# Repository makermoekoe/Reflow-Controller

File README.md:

# Reflow-Controller

</a>

The Reflow-Controller was built to control different kinds of reflow ovens, hotplates and whatever is coming to my mind in the future. It is based on the ESP32-S2 ([datasheet](https://www.espressif.com/sites/default/files/documentation/esp32-s2_datasheet_en.pdf)) and thus can be programmed to be used with a WiFi App or whatever. Nevertheless, it has an onboard OLED display and three buttons included to be used as a standalone solution either.

The [Youtube video](https://youtu.be/nffLDqJwJ3Q) shows the assembly of a complete reflow oven system and the first tests.

## Build & flash :
Using Visual Studio : Import "code" folder as project folder. Connect the pcb via usb, put the S1 switch to the lower position, hold and press GPIO0-button while resetting with the reset-button. ESP32 should come up as a serial port device. Select that corresponding port for flashing. Edit platformio.ini file and set the upload_port setting corresponding to your serial port device (COMxx on Windows, /dev/ttyUSBx on linux or /dev/cu.usbmodem01 as stated by makermoekoe (original projects author).
Press compile & upload button.

Using Arduino IDE :
Import main.cpp file contents as a new sketch.
Add "https://raw.githubusercontent.com/espressif/arduino-esp32/gh-pages/package_esp32_dev_index.json" as additional board manager URL in Arduino IDE preferences.
Connect the pcb via usb, put the S1 switch to the lower position, hold and press GPIO0-button while resetting with the reset-button. ESP32 should come up as a serial port device. Select that corresponding port for flashing in Arduino (Port setting where the board selection is also located, in "Tools" - Menu)
Then select ESP32S2-Dev Module as board in Arduino. You can make all ESP32-related flash & chip configs there too. The settings I use are :
-"Use CDC on boot" - Enabled
-"CPU Frequency" - 240MHz
-"Core Debug Level" - Warn

All others left by default / select the ones you think fits best.

Libraries required as dependency for the project in Arduino (as for 2.0.3 version I currently use, install them via Arduino Library Manager) :
- PID by Brett Beauregard - v 1.2.1
- FastLED by Daniel Garcia - v 3.5.0
- U8G2 by Oliver Kraus - v 2.33.15
- MAX6675 Library by Adafruit - v 1.1.0
- Smoothed by Matthew Fryer - v 1.2
- ESPAsync-WifiManager and all it`s dependencies (install via IDE library manager) - https://github.com/khoih-prog/ESPAsync_WiFiManager

Lib-versions are the latest ones when writing this.

## Wifi - Setup :
Wifi will (currently!?) NOT work correctly when the board is powered by USB.
This means, you can flash via USB without external power to the board, but, as the initial wifi-setup is blocking the normal program, you will need to power via external power, to get wifi set up correctly. Once wifi is set up, "normal" program will run as soon as wifi connected.
Make sure to select the default 4MB flash partitioning scheme with SPIFFS when flashing.
Process should be done as follows :
Compile & flash => switch to external power => configure wifi by connecting to the esp32-provided AP => restart board on external. You can and should monitor the serial output via USB for the first startup via serial console anyhow, as it will show you debug info and the default wifi-password for the config ap. The caption page of the AP to do the wifi settings is listening on 192.168.4.1:80 once the AP is up.

## OTA-Flash :
Once the board is connected to wifi, you can flash it over the air from then on. Simply select the network-connection port in Arduino, that should come up a few seconds after the board is powered and connected to wifi. Only downside/bug I found so far, is that often the flashing process in Arduino doesnt get the successful flash response and therefore keeps hanging in flash mechanism - making a restart of the IDE necessary. Apart from that, OTA works fine.

(Note from p1ngb4ck, adding this section : ) At the time of writing this, I did not yet find out, how to make the esptool.py settings in Visual Studio Code to be able to make the ESP32 chip settings (USB-CDC, SPIFFS etc etc). Therefore I currently use Arduino 2.0.3 IDE myself. Visual Studio Code has the advantage though, not to have to download&install dependencies (libraries) manually though. If anybody share some light into how to make these settings correctly in Visual Studio Code - you are mostly welcome to add this info by posting to issues section. TY.

Lots of thanks for this great project to makermoekoe. Please watch his video !!!

## Features of the PCB:

- ESP32-S2 MCU
- 2x MAX6675 thermocouple sensor input
- 2x Fan output (inductive loads/flyback diodes included)
- 2x Solid state relay output
- 3x User button
- 1x APA102 user LED
- 1x Buzzer
- 1x Servo motor output
- 0,96" OLED display
- Optional ACDC converter (HLK-PM05, HLK-PM12) which can be separated if not used
- Optional I2C (QWIIC) connector

## GPIOs

The ESP32-S2 is connected like this:

Function | GPIO | Mode
-------- | -------- | --------
SSR1 | GPIO1 | Output
SSR2 | GPIO2 | Output
Servo | GPIO3 | Output
Fan1 | GPIO5 | Output
Fan2 | GPIO6 | Output
CLK | GPIO7 | SPI
MISO | GPIO9 | SPI
MOSI | GPIO11 | SPI
CS1 | GPIO12 | SPI
CS2 | GPIO13 | SPI
Buzzer | GPIO15 | Output
USB D- | GPIO19 | CDC
USB D+ | GPIO20 | CDC
SDA | GPIO33 | I2C
SCL | GPIO35 | I2C
Button1 | GPIO36 | Input
Button2 | GPIO39 | Input
Button3 | GPIO40 | Input
LED CLK | GPIO37 | LED
LED DATA | GPIO38 | LED
OLED RST | GPIO45 | Output

## ACDC power supply

The upper part of the PCB can be used as a power supply for the whole board as well as the higher voltage outputs (SSRs, Fans). If not used, it can be separated from the main board and may be used in another project where an ACDC adapter is needed.

The main board is equipped with an LM1117 3.3v voltage regulator which can be feed with 15v max. The output voltage of the ACDC power supply is the voltage for the SSR and the fan output channels. If you wanna use a servo motor in your project, make sure that the power supply has the correct voltage for the motor (probably 5v).

The HLK-PMXX module for the upper part of the PCB can be placed in two ways - on the bottom or on the top side. This gives the possibility to mount the whole PCB behind an acrylic glass (or whatever) so that the buttons as well as the OLED display are accessible. The two jumpers can then be used to select which signal is VCC and which one is GND. **Keep in mind that there are high voltage pins on the top side of the PCB when mounting the power supply on the bottom side! I've designed a 3D-printable cover, so that these pins cannot be touched accidentally. (Should be mounted in both cases)**

The board can also be powered via USB-C, but keep in mind that the output channels and the servo motor are not powered in this case (initially it is just available for flashing the board).

## Case & Spacer

As I wanna hide the whole PCB behind an acrylic glass (transparent) I've designed a simple case for the high voltage pins at the top and a spacer at the bottom of the PCB. In the end, the acrylic glass will be laser-cutted with some bridges for the buttons. Distance between PCB and acrylic glass is 5mm.

</a>

## Assembled reflow oven

</a>

</a>

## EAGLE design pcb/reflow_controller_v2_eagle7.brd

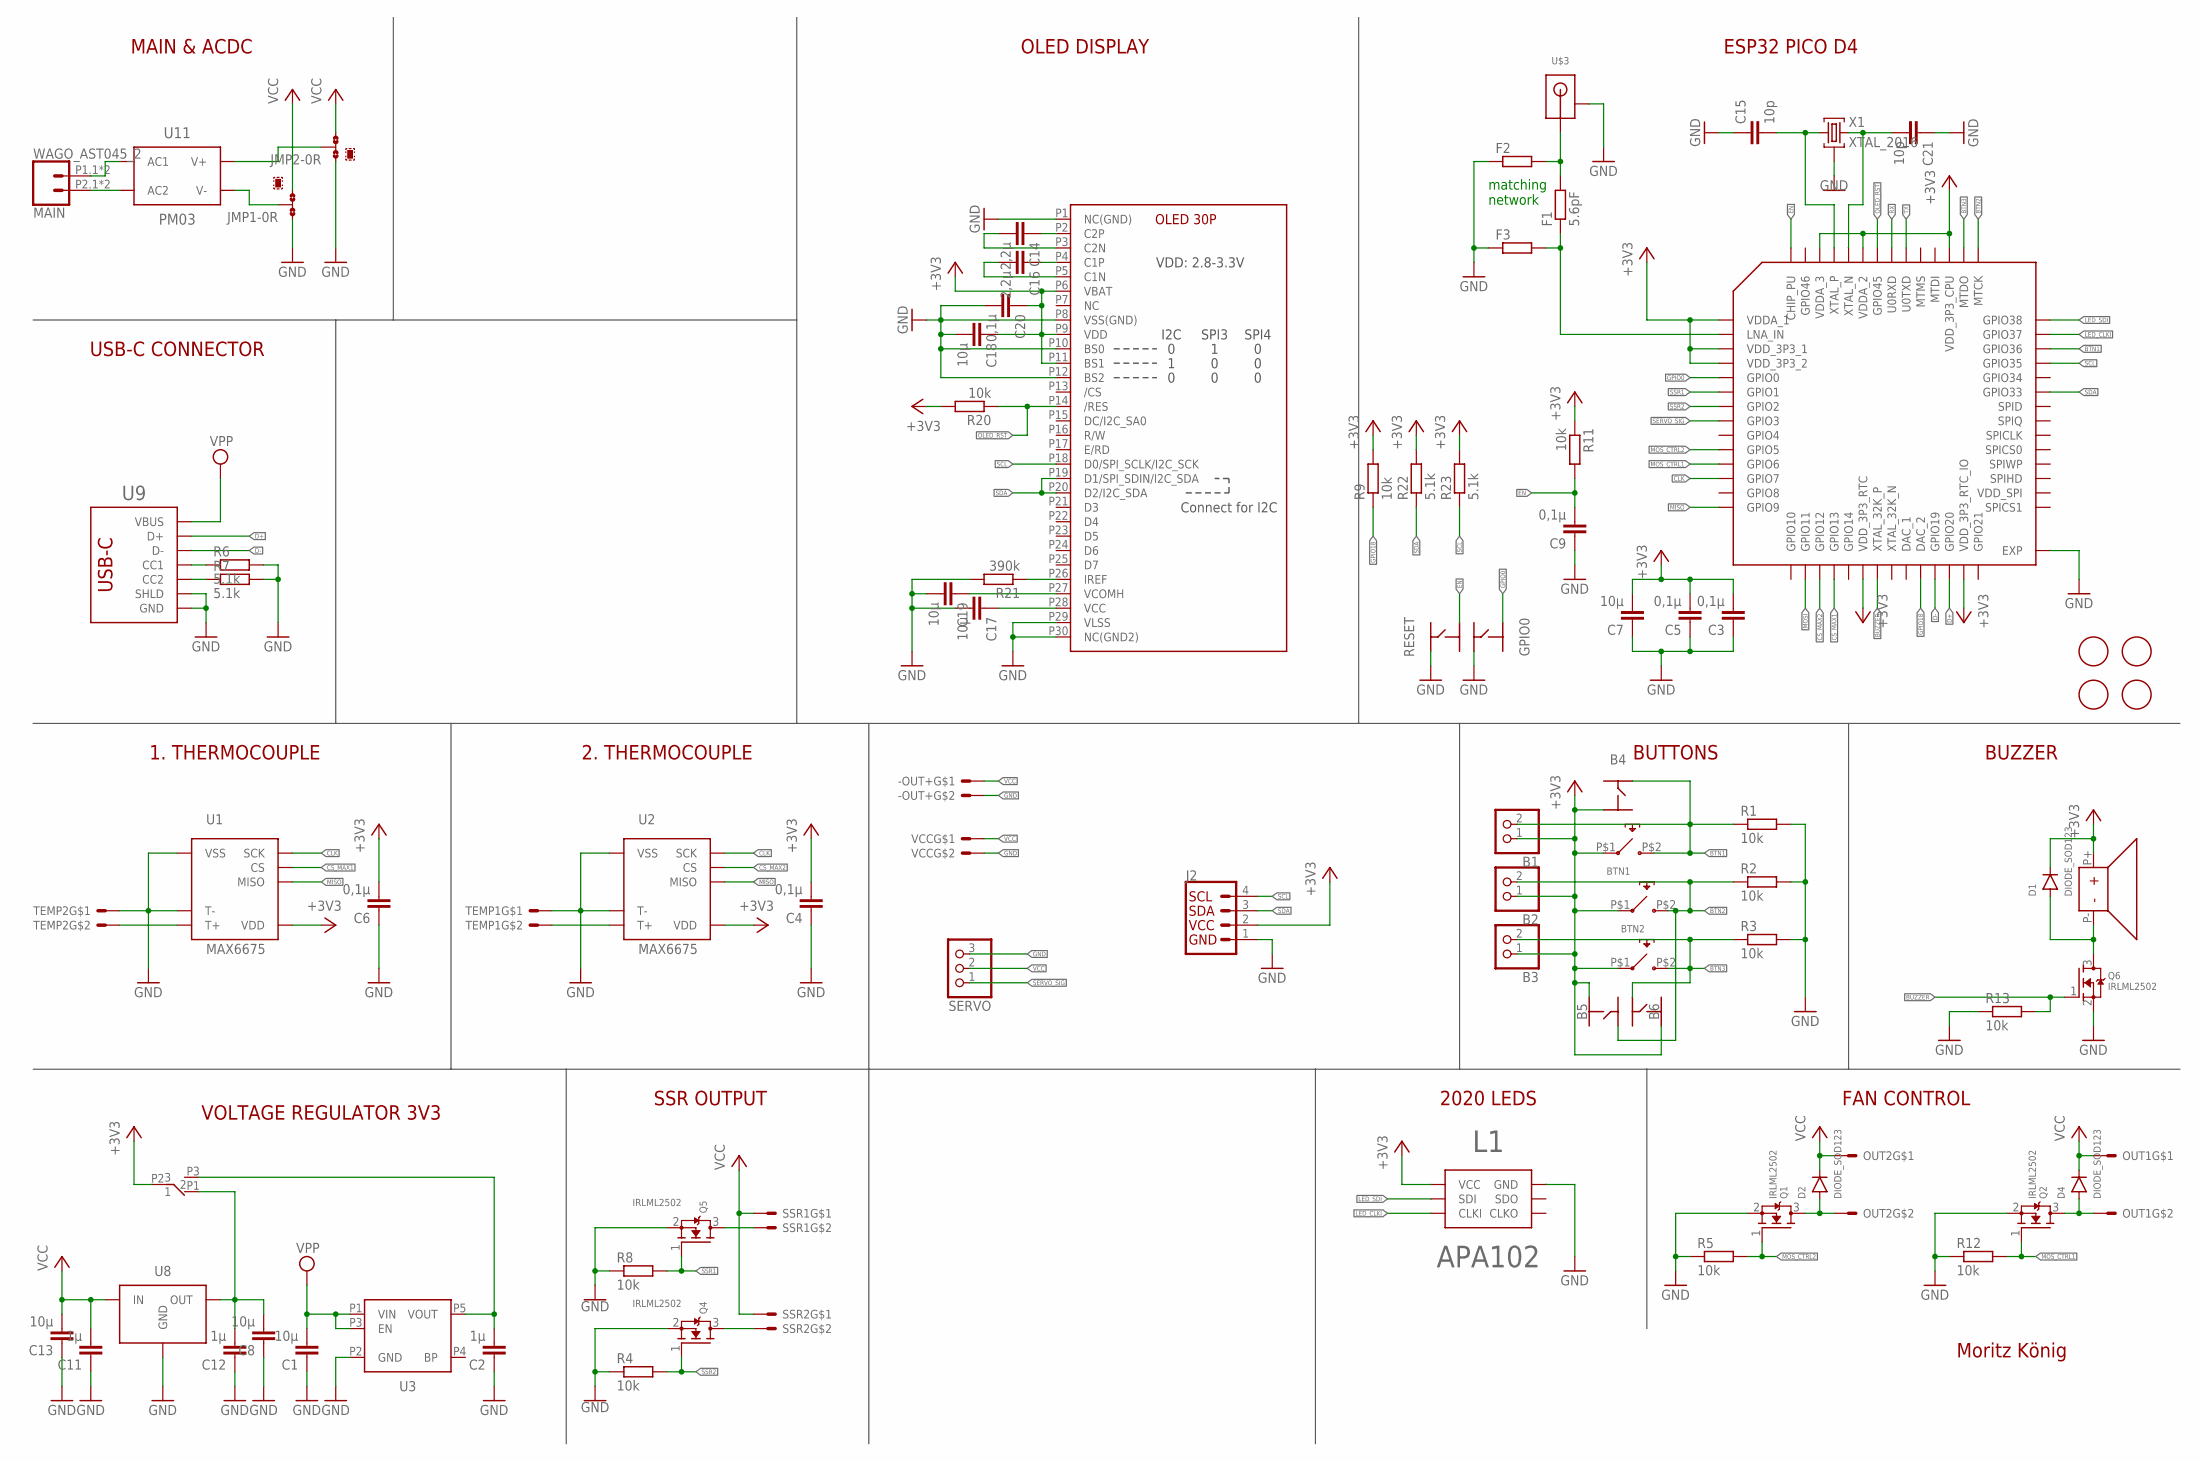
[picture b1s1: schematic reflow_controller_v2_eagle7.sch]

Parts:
-OUT+: MOLEX_2MM_2P
B1, B2, B3: PINHD-1X02_2.00; 1X02M
B4, B5, B6: BUTTON_4PIN_TS-1070A; BUTTON_WHITE_SMD
BTN1, BTN2, BTN3: BUTTON_6X6_SILICON; BUTTON_SILICON
C1, C7, C8, C13, C17, C18, C19: 10µ; C0603
C2, C11, C12: 1µ; C0603
C3, C4, C5, C6, C9, C20: 0,1µ; C0603
C14, C16: 2,2µ; C0603
C15, C21: 10p; C0603
D1, D2, D4: DIODE_SOD123; SOD123
ESP: ESP32_S2_QFN56_NEW; QFN56_7X7
F1: 5.6pF; R0402
F2, F3: R-EU-0402-WOKEEPOUT; R0402
GPIO0: BUTTON_4PIN_TS_1177; TS-1177-C-B-B
J2: QWIIC_CONNECTORJS-1MM; 1X04_1MM_RA
JMP1, JMP2: 0R-JUMPA; A0R-JMP
L1: APA102_2020
MAIN: WAGO_AST045_2
OUT1, OUT2: MOLEX_2MM_2P
Q1, Q2, Q4, Q5, Q6: IRLML2502; SOT23
R1, R2, R3, R4, R5, R8, R9, R11, R12, R13, R20: 10k; R0603
R6, R7, R22, R23: 5.1k; R0603
R21: 390k; R0603
RESET: BUTTON_4PIN_TS_1177; TS-1177-C-B-B
S1: SWITCH_MS-22C01-G010; MS-22C01-G010
SERVO: PINHD-1X03_2.54; 1X03
SSR1, SSR2: MOLEX_2MM_2P
TEMP1, TEMP2: MOLEX_2MM_2P
U1, U2: MAX6675; SO8
U3: RT9193_SC70-5; SC-70-5
U4: OLD_096_SSD1306_30P_2B; OLED_096_30P_B
U8: LM1117; SOT223
U9: USB_C_C393939; USBC_C393939
U10: MLT-5030-BUZZER
U11: HILINK_PM03
U$1, U$2, U$4, U$5: FIDUCIAL; FIDUCIAL_1MM
U$3: UFL_ANT_CONNECTOR
VCC: MOLEX_2MM_2P
X1: XTAL_2016; XTYL_2016

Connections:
+3V3: B1.1, B2.1, B3.1, B4.P$2 (3), B5.P$2 (3), B6.P$2 (3), BTN1.P$1 (P1), BTN2.P$1 (P1), BTN3.P$1 (P1), C3.2, C4.2, C5.2, C6.2, C7.2, C18.1, C20.1, D1.P$2 (C), ESP.1 (VDDA_1), ESP.3 (VDD_3P3_1), ESP.4 (VDD_3P3_2), ESP.20 (VDD_3P3_RTC), ESP.27 (VDD_3P3_RTC_IO), ESP.45 (VDD_3P3_CPU), ESP.51 (VDDA_2), ESP.54 (VDDA_3), J2.2 (VCC), L1.P1 (VCC), L1.P1.1 (VCC), R9.2, R11.1, R20.2, R22.2, R23.2, S1.P2 (2), U1.4 (VDD), U2.4 (VDD), U4.P6 (VBAT), U4.P9 (VDD), U4.P11 (BS1), U10.P+
ANTENNA1: F1.2, F2.2, U$3.ANT
BTN1: B1.2, B4.P$4 (2), BTN1.P$2 (P2), ESP.40 (GPIO36), R1.1
BTN2: B2.2, B5.P$4 (2), BTN2.P$2 (P2), ESP.43 (MTCK), R2.1
BTN3: B3.2, B6.P$4 (2), BTN3.P$2 (P2), ESP.44 (MTDO), R3.1
BUZZER: ESP.21 (XTAL_32K_P), Q6.1 (G), R13.2
CLK: ESP.12 (GPIO7), U1.5 (SCK), U2.5 (SCK)
CS_MAX1: ESP.18 (GPIO13), U1.6 (CS)
CS_MAX2: ESP.17 (GPIO12), U2.6 (CS)
D+: ESP.26 (GPIO20), U9.A6 (D+), U9.B6 (D+)
D-: ESP.25 (GPIO19), U9.A7 (D-), U9.B7 (D-)
EN: C9.2, ESP.56 (CHIP_PU), R11.2, RESET.P4 (4)
GND: -OUT+.2, C1.1, C2.1, C3.1, C4.1, C5.1, C6.1, C7.1, C8.1, C9.1, C11.1, C12.1, C13.1, C15.1, C17.2, C18.2, C19.2, C20.2, C21.1, ESP.57 (EXP), F2.1, F3.1, GPIO0.P1 (1), J2.1 (GND), JMP1.1, JMP2.1, L1.P6 (GND), L1.P6.1 (GND), Q1.2 (S), Q2.2 (S), Q4.2 (S), Q5.2 (S), Q6.2 (S), R1.2, R2.2, R3.2, R4.1, R5.1, R6.2, R7.2, R8.1, R12.1, R13.1, R21.2, RESET.P1 (1), SERVO.3, TEMP1.1, TEMP2.1, U1.1 (VSS), U1.2 (T-), U2.1 (VSS), U2.2 (T-), U3.P2 (GND), U4.P1 (NC(GND)), U4.P8 (VSS(GND)), U4.P10 (BS0), U4.P12 (BS2), U4.P29 (VLSS), U4.P30 (NC(GND2)), U8.1 (GND), U9.A1B12 (GND), U9.B1A12 (GND), U9.S1 (SHLD), U9.S2 (SHLD), U9.S3 (SHLD), U9.S4 (SHLD), U$3.P1.- (GND), U$3.P2.- (GND), VCC.2, X1.P2 (G), X1.P4 (G)
GPIO0: ESP.5 (GPIO0), GPIO0.P4 (4)
GPIO18: ESP.24 (DAC_2), R9.1
LED_CLKI: ESP.41 (GPIO37), L1.P5 (CLKI)
LED_SDI: ESP.42 (GPIO38), L1.P4 (SDI)
MISO: ESP.14 (GPIO9), U1.7 (MISO), U2.7 (MISO)
MOSI: ESP.16 (GPIO11)
MOS_CTRL1: ESP.11 (GPIO6), Q2.1 (G), R12.2
MOS_CTRL2: ESP.10 (GPIO5), Q1.1 (G), R5.2
unnamed: MAIN.P1.1 (1), MAIN.P1.2 (1), U11.AC1
unnamed: TEMP2.2, U1.3 (T+)
unnamed: MAIN.P2.1 (2), MAIN.P2.2 (2), U11.AC2
unnamed: ESP.2 (LNA_IN), F1.1, F3.2
unnamed: D2.P$1 (A), OUT2.2, Q1.3 (D)
unnamed: D1.P$1 (A), Q6.3 (D), U10.P-
unnamed: D4.P$1 (A), OUT1.2, Q2.3 (D)
unnamed: Q4.3 (D), SSR2.2
unnamed: Q5.3 (D), SSR1.2
unnamed: C15.2, ESP.53 (XTAL_P), X1.P1 (1)
unnamed: C21.2, ESP.52 (XTAL_N), X1.P3 (2)
unnamed: TEMP1.2, U2.3 (T+)
unnamed: JMP2.2, U11.V+
unnamed: C8.2, C12.2, S1.P1 (1), U8.2 (OUT), U8.4 (OUT)
unnamed: C14.1, U4.P2 (C2P)
unnamed: R7.1, U9.B5 (CC2)
unnamed: C14.2, U4.P3 (C2N)
unnamed: C16.2, U4.P5 (C1N)
unnamed: R21.1, U4.P26 (IREF)
unnamed: C2.2, S1.P3 (3), U3.P5 (VOUT)
unnamed: JMP1.2, U11.V-
unnamed: R6.1, U9.A5 (CC1)
unnamed: C16.1, U4.P4 (C1P)
unnamed: C17.1, U4.P28 (VCC)
unnamed: C19.1, U4.P27 (VCOMH)
OLED_RST: ESP.50 (GPIO45), R20.1, U4.P14 (/RES)
RX: ESP.49 (U0RXD)
SCL: ESP.39 (GPIO35), J2.4 (SCL), R23.1, U4.P18 (D0/SPI_SCLK/I2C_SCK)
SDA: ESP.37 (GPIO33), J2.3 (SDA), R22.1, U4.P19 (D1/SPI_SDIN/I2C_SDA), U4.P20 (D2/I2C_SDA)
SERVO_SIG: ESP.8 (GPIO3), SERVO.1
SSR1: ESP.6 (GPIO1), Q5.1 (G), R8.2
SSR2: ESP.7 (GPIO2), Q4.1 (G), R4.2
TX: ESP.48 (U0TXD)
VCC: -OUT+.1, C11.2, C13.2, D2.P$2 (C), D4.P$2 (C), JMP1.3, JMP2.3, OUT1.1, OUT2.1, SERVO.2, SSR1.1, SSR2.1, U8.3 (IN), VCC.1
VPP: C1.2, U3.P1 (VIN), U3.P3 (EN), U9.A4B9 (VBUS), U9.B4A9 (VBUS)

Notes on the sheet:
Moritz König
VOLTAGE REGULATOR 3V3
2020 LEDS
ESP32 PICO D4
matching network
OLED DISPLAY
USB-C CONNECTOR
MAIN & ACDC
1. THERMOCOUPLE
2. THERMOCOUPLE
BUTTONS
BUZZER
FAN CONTROL
SSR OUTPUT

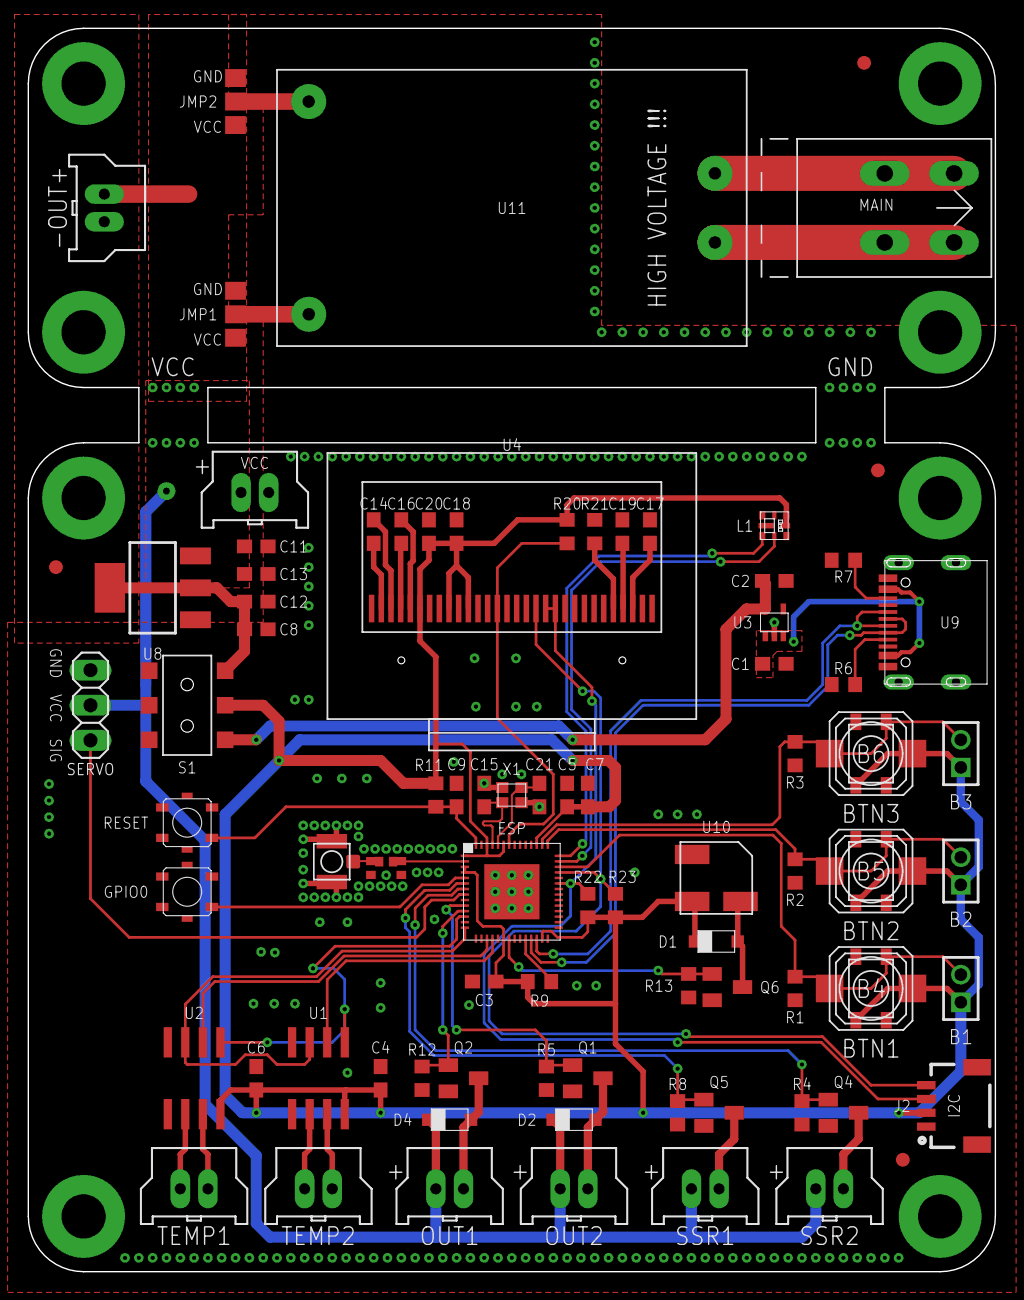
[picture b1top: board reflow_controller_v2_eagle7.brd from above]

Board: 2 copper layers, 70.0 x 90.0 mm, 88 parts (0 on the bottom side), 53 nets.

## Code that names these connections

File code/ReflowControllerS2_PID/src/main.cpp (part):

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#define SCL_PIN         35
#define APA102_SDI_PIN  38
#define APA102_CLK_PIN  37
#define OLED_RST_PIN    45
#define CS_MAX1_PIN     13
#define CS_MAX2_PIN     12
#define MISO_PIN        9
#define MOSI_PIN        11
#define CLK_PIN         7

#define MOS_CTRL1_PIN   5
#define MOS_CTRL2_PIN   6
#define SSR1_PIN        1
#define SSR2_PIN        2
#define SERVO_PIN       3
#define BUZZER_PIN      15
#define BTN1_PIN        36
#define BTN2_PIN        39
#define BTN3_PIN        40


#define NUM_LEDS        1
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
#define WIDTH 128
#define HEIGHT 64
U8G2_SSD1306_128X64_NONAME_F_HW_I2C u8g2(U8G2_R0, /* reset=*/ OLED_RST_PIN, /* clock=*/ SCL_PIN, /* data=*/ SDA_PIN);

double pid_setpoint, pid_input, pid_output;
double Kp = 10, Ki = 3, Kd = 2;
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const int PWMResolution = 10;                       //12 bits 0-4095


MAX6675 thermocouple1(CLK_PIN, CS_MAX2_PIN, MISO_PIN);
MAX6675 thermocouple2(CLK_PIN, CS_MAX1_PIN, MISO_PIN);

float current_temperature1 = 0.0;
float current_temperature2 = 0.0;
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  Serial.begin(115200);
  Serial.println("start");

  pinMode(BTN1_PIN, INPUT);
  pinMode(BTN2_PIN, INPUT);
  pinMode(BTN3_PIN, INPUT);

  pinMode(CS_MAX1_PIN, OUTPUT);
  pinMode(CS_MAX2_PIN, OUTPUT);
  digitalWrite(CS_MAX1_PIN, LOW);
  digitalWrite(CS_MAX2_PIN, LOW);

  pinMode(SSR1_PIN, OUTPUT);
  pinMode(SSR2_PIN, OUTPUT);
  digitalWrite(SSR1_PIN, LOW);
  digitalWrite(SSR2_PIN, LOW);
  

  delay(100);
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  FastLED.setBrightness(100);
  delay(100);

  pinMode(BUZZER_PIN, OUTPUT);
  digitalWrite(BUZZER_PIN, LOW);

  ledcSetup(PWMChannel, PWMFreq, PWMResolution);
  ledcAttachPin(BUZZER_PIN, PWMChannel);
  ledcWrite(PWMChannel, dutyCycle);

  ledcWrite(PWMChannel, 500);
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unsigned long t_pid_on = millis() + 400;

void loop() {
  if(digitalRead(BTN1_PIN) == 1){
    leds[0] = CRGB::Blue;
    FastLED.show();
    delay(50);
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    int wait_time_increase = 300;
    bool set_process = false;

    while (digitalRead(BTN1_PIN) == 1){
      if(millis() >= t_btn_pressed + wait_time_increase && !set_process){
        wait_time_increase = 80;
        t_btn_pressed = millis();
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    leds[0] = CRGB::Black;
    FastLED.show();
  }
  else if(digitalRead(BTN2_PIN) == 1){
    leds[0] = CRGB::Blue;
    FastLED.show();
    delay(50);
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    int wait_time_increase = 300;
    bool set_process = false;
    
    while (digitalRead(BTN2_PIN) == 1){
      if(millis() >= t_btn_pressed + wait_time_increase && !set_process){
        leds[0] = CRGB::Orange;
        FastLED.show();
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    leds[0] = CRGB::Black;
    FastLED.show();
  }
  else if(digitalRead(BTN3_PIN) == 1){
    leds[0] = CRGB::Blue;
    FastLED.show();
    delay(50);
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    update_display();

    unsigned long t_btn_pressed = millis();
    while (digitalRead(BTN3_PIN) == 1){
      if(millis() >= t_btn_pressed + 800){
        leds[0] = CRGB::Orange;
        FastLED.show();
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
      msg2display_bot = String(pid_output);// + ", " + String(window_start_time);
      if(pid_output > 10){
        digitalWrite(SSR1_PIN, HIGH);
        leds[0] = CRGB::Red;
        FastLED.show();
        t_pid_on = millis();
      }
    }

    if(millis() > t_pid_on + pid_output && digitalRead(SSR1_PIN)){
      digitalWrite(SSR1_PIN, LOW);
      leds[0] = CRGB::Yellow;
      FastLED.show();
    }
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    //   window_start_time += window_size;
    // }
    // if(pid_output > now - window_start_time){
    //   digitalWrite(SSR1_PIN, HIGH);
    //   leds[0] = CRGB::Red;
    //   FastLED.show();
    // } 
    // else{
    //   digitalWrite(SSR1_PIN, LOW);
    //   leds[0] = CRGB::Yellow;
    //   FastLED.show();
    // }
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
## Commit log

2022-01-21 Initial commit, basic structure
2022-02-01 added PCB files and schematics
2022-02-01 added first docs
2022-02-03 updated docs
2022-02-23 updated docs and added cases + images
2022-03-09 added code example
2022-03-12 updated schematics and code
2022-03-15 updated code with working reflow profile
2022-03-16 added selectable reflow profiles to gui
2022-04-05 added reflow oven pictures
2022-04-10 updated docs with video link
2022-04-12 updated final controller code
2022-04-21 added gerber files
2022-04-21 added .sch and .brd for eagle7.x
2022-08-28 Added file for component sourcing
    Component sources for most parts. Some connectors could not be found
2022-12-27 Create BOM CSV with annotations
2023-01-25 buzzer pwm & i2c init fixes
    Added separate PWM channel for buzzer
    Removed unnecessary doubled wire initialization (thanks to dayars hint on OLED issue of original repo)
2023-01-25 remove unnecessary serial print outputs
2023-01-25 Add compile & flash info for VS Code & Arduino IDEs
2023-01-25 remove fixed version tags to select latest versions
    After making minor changes to pwm (buzzer) and i2c initialization, fixed older versions for the libs are unnecessary. Works fine with latest versions now.
2023-01-25 Add files via upload
    Working BOM as of 2023-01-25
2023-01-27 Add ESPAsync-WifiManager & OTA support
    added wifi support using ESPAsync-WifiManager & OTA via direct Arduino OTA (not Webserver based currently)
2023-01-27 Add Wifi & OTA info / short notice
2023-01-27 Remove obsolete SPIFFS & WiFi sentence
2023-01-27 formatting changes
2023-01-27 update platformio.ini for wifi dependencies
2023-11-21 added pdf schematics
2023-11-21 added 3d models

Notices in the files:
parts and their libraries:
SparkFun-Connectors: Licensing: Creative Commons ShareAlike 4.0 International - https://creativecommons.org/licenses/by-sa/4.0
